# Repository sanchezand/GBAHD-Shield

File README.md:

# gbaHD Shield
This is a shield for the [gbaHD project](https://github.com/zwenergy/gbaHD).  

Has the following features.
- Connects via female headers to the Edge board (shield)
- Has a FFC 40, 32 and 34 pin connector for GBA LCD connector.
- Has a FFC 20 pin connector for controls with a wire up board.
- Has a ATMEGA328p for using a SNES Classic connector to control the GBA.
- **Both FFC cables need to be opposite side**

## Issues
- Havent had the chance to fully test the controller extension board, but the controller port on it works.
- Controller extension board needs to be made bigger and separate the button from the LED and the LED from the controller port.
- No case made for it yet
- GND pin on the breakout board needs to be moved (doesnt affect anything)
- Labels on breakout board need to be made bigger

## Contributing
If you wish to contribute, see something wrong or want to add a feature please make a pull request or leave an issue!

## BOM
|Reference	|Value								|
|---------	|--------							|
|C1, C2		|22pF									|
|C3			|100nF								|
|R1			|10K ohm									|
|R2			|120 ohm (or change for your LED)	|
|D1			|5mm LED or<br />TJ-L5FPTGCRMFCSFLC2R-A5	|
|U2			|ATMEGA328p-AU						|
|X1			|16MHz Crystal SMD-3225			|
|SW1			|XKB-TS-1185EC-C-D-B				|
|SW2			|XKB_XKB5858-Z-C					|
|J1			|JUSHUO_AFC01-S40FCC-00			|
|J2			|PinHeader 2x08 2.54mm			|
|J3, J9		|JUSHUO_AFC01-S20FCC-00			|
|J5			|JUSHUO_AFC07-S34FCC-00			|
|J7			|JUSHUO_AFC01-S32FCC-00			|
|J4			|PinHeader 2x10 2.54mm			|
|P1, P2		|Wii Expansion Port				|
|EXTRA 1		|PinHeader 1x08 2.54mm			|
|EXTRA 2		|PinHeader 1x06 2.54mm			|

## Programming the MCU
In order to program the MCU, you need an arduino to use as ISP.  
Use the following image to wire up an arduino to the board to program it.  
**I would also recomend not programming it while seated in the FPGA board.**
  
After wiring the board, follow this tutorial to flash the bootloader and the sketch to the board.  
[ICSP Tutorial](https://www.arduino.cc/en/pmwiki.php?n=Tutorial/ArduinoISP)  
  
The Arduino code requires the [NintendoExtensionCtrl](https://github.com/dmadison/NintendoExtensionCtrl) library.

## Version 1 vs Version 2
- __Removed SNES connector for an classic controller connector__
- Made the PCB bigger and uses lower pins to improve stability
- Added future proof pins to the edge board.
- Panelized the board to lower the amount of PCBs needed
- Added an "Expansion" board to relocate the controller port and add an LED and power switch (which needs to desolder old switch and be wired to the Spartan board)
- Made the breakout board bigger and added more extra pins.
- Changed FFC connectors (except 34 pin) to use a clamp down connector.

## Images

## LICENSE
This documentation describes Open Hardware and is licensed under the CERN OHL v. 1.2.
You may redistribute and modify this documentation under the terms of the CERN OHL v.1.2. (http://ohwr.org/cernohl). This documentation is distributed WITHOUT ANY EXPRESS OR IMPLIED WARRANTY, INCLUDING OF MERCHANTABILITY, SATISFACTORY QUALITY AND FITNESS FOR A PARTICULAR PURPOSE. Please see the CERN OHL v.1.2 for applicable conditions.

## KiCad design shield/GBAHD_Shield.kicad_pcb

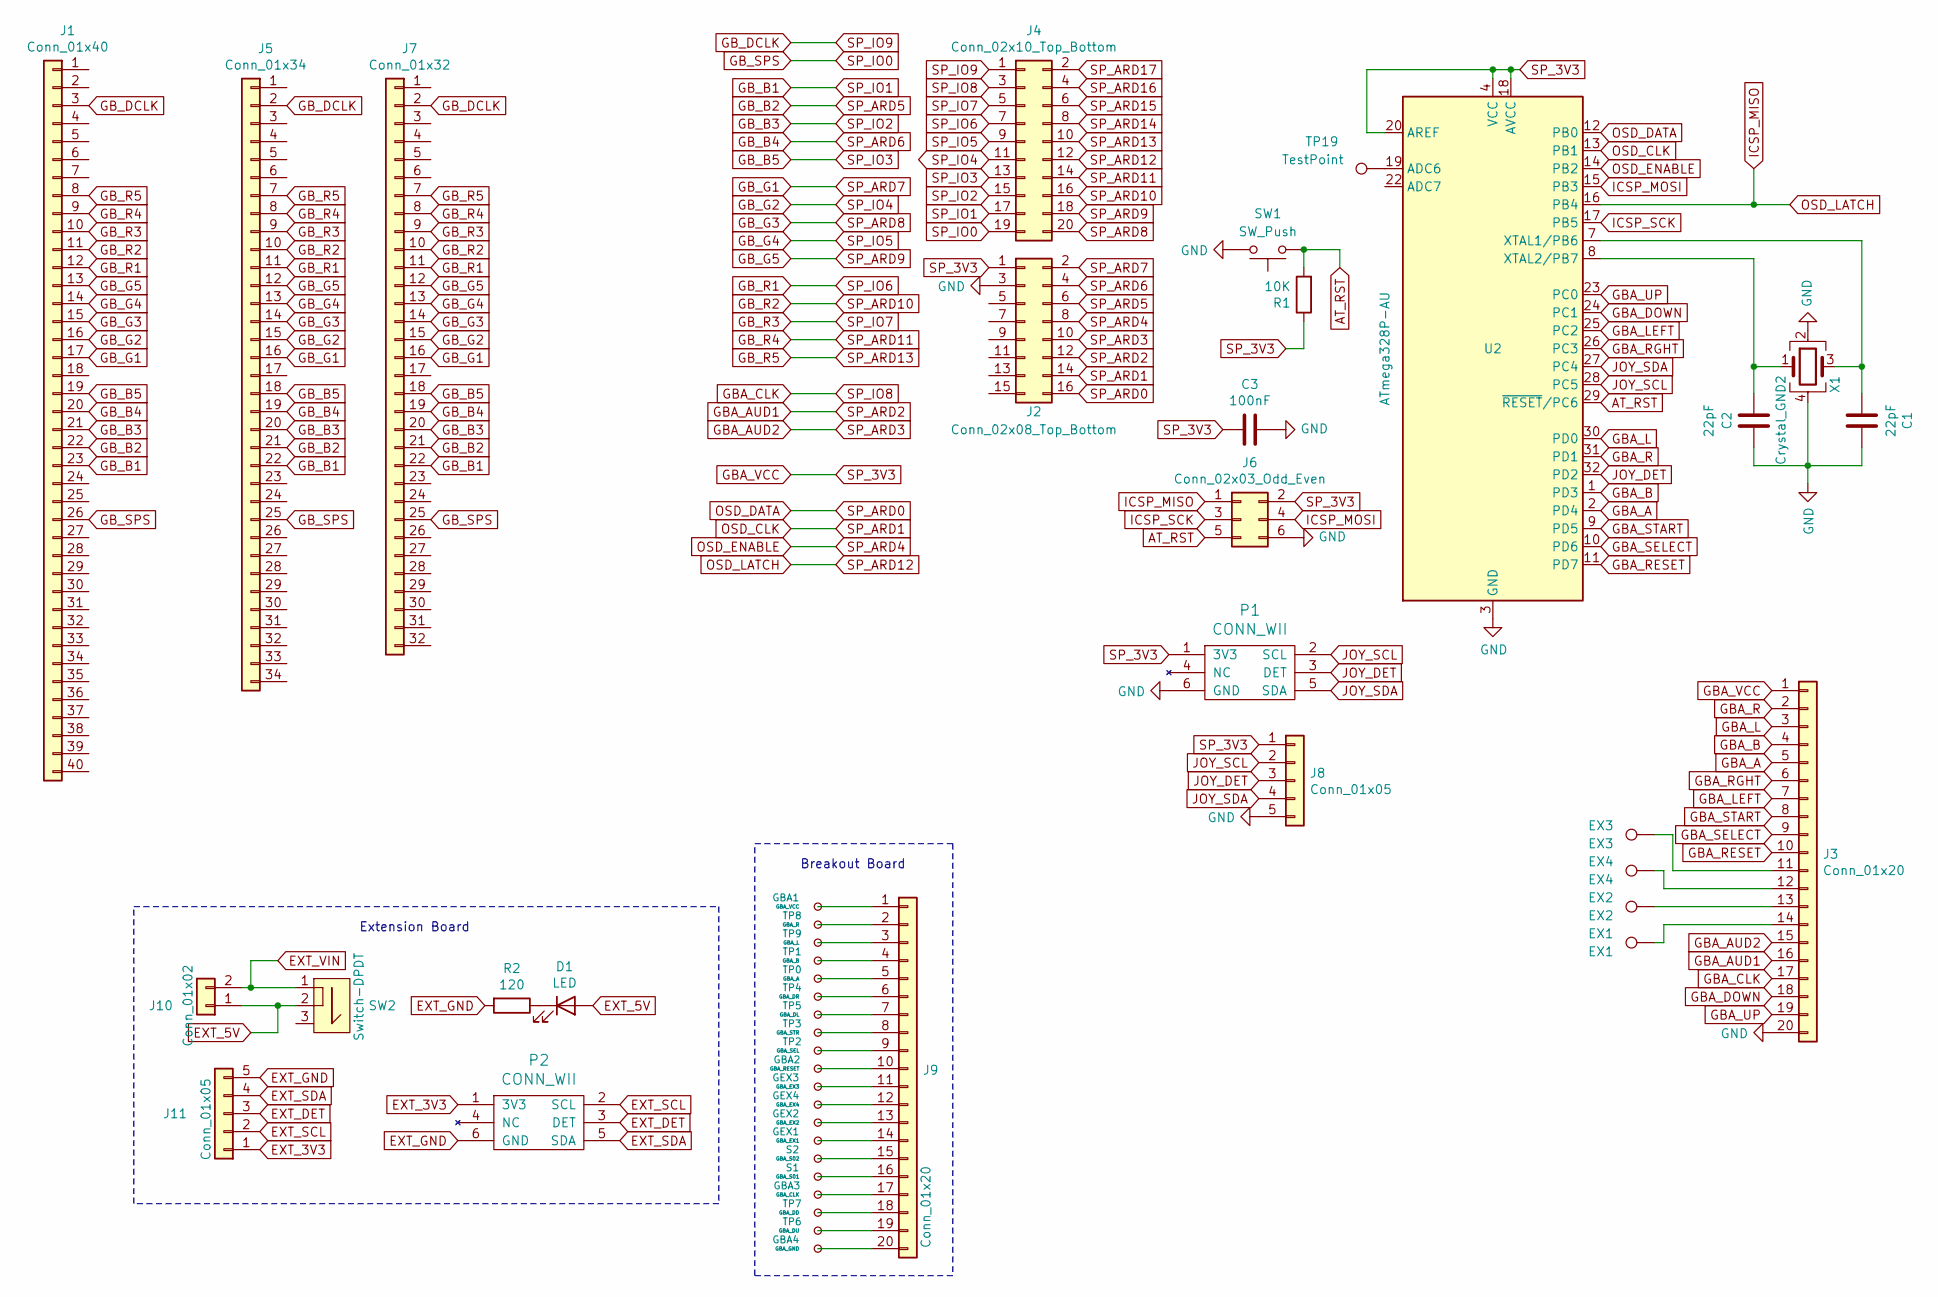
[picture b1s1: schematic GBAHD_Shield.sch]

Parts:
C1, C2: 22pF; C_0805_2012Metric_Pad1.18x1.45mm_HandSolder
C3: 100nF; C_0805_2012Metric_Pad1.18x1.45mm_HandSolder
D1: LED; LED_D5.0mm_FlatTop
EX1: EX1; SOLDER_PAD
EX2: EX2; SOLDER_PAD
EX3: EX3; SOLDER_PAD
EX4: EX4; SOLDER_PAD
GBA1: GBA_VCC; SOLDER_PAD
GBA2: GBA_RESET; SOLDER_PAD
GBA3: GBA_CLK; SOLDER_PAD
GBA4: GBA_GND; SOLDER_PAD
GEX1: GBA_EX1; SOLDER_PAD
GEX2: GBA_EX2; SOLDER_PAD
GEX3: GBA_EX3; SOLDER_PAD
GEX4: GBA_EX4; SOLDER_PAD
J1: Conn_01x40; JUSHUO_AFC01-S40FCC-00
J2: Conn_02x08_Top_Bottom; PinHeader_2x08_P2.54mm_Vertical
J3, J9: Conn_01x20; JUSHUO_AFC01-S20FCC-00
J4: Conn_02x10_Top_Bottom; PinHeader_2x10_P2.54mm_Vertical
J5: Conn_01x34; JUSHUO_AFC07-S34FCC-00
J6: Conn_02x03_Odd_Even; PinHeader_2x03_P2.54mm_Vertical
J7: Conn_01x32; JUSHUO_AFC01-S32FCC-00
J8, J11: Conn_01x05; PinHeader_1x05_P2.54mm_Horizontal
J10: Conn_01x02; PinHeader_1x02_P2.54mm_Horizontal
P1, P2: CONN_WII
R1: 10K; R_0805_2012Metric_Pad1.20x1.40mm_HandSolder
R2: 120; R_0805_2012Metric_Pad1.20x1.40mm_HandSolder
S1: GBA_S01; SOLDER_PAD
S2: GBA_S02; SOLDER_PAD
SW1: SW_Push; XKB-TS-1185EC-C-D-B
SW2: Switch-DPDT; XKB_XKB5858-Z-C
TP0: GBA_A; SOLDER_PAD
TP1: GBA_B; SOLDER_PAD
TP2: GBA_SEL; SOLDER_PAD
TP3: GBA_STR; SOLDER_PAD
TP4: GBA_DR; SOLDER_PAD
TP5: GBA_DL; SOLDER_PAD
TP6: GBA_DU; SOLDER_PAD
TP7: GBA_DD; SOLDER_PAD
TP8: GBA_R; SOLDER_PAD
TP9: GBA_L; SOLDER_PAD
TP19: TestPoint; SOLDER_PAD
U2: ATmega328P-AU; TQFP-32_7x7mm_P0.8mm
X1: Crystal_GND2; Crystal_SMD_3225-4Pin_3.2x2.5mm

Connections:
AT_RST: J6.5, R1.2, SW1.1, U2.29 (~RESET~/PC6)
EXT_3V3: J11.1, P2.1 (3V3)
EXT_5V: D1.2 (A), J10.1, SW2.2
EXT_DET: J11.3, P2.3 (DET)
EXT_GND: J11.5, P2.6 (GND), R2.2
EXT_SCL: J11.2, P2.2 (SCL)
EXT_SDA: J11.4, P2.5 (SDA)
EXT_VIN: J10.2, SW2.1
GBA_A: J3.5, U2.2 (PD4)
GBA_AUD1: J2.12, J3.16
GBA_AUD2: J2.10, J3.15
GBA_B: J3.4, U2.1 (PD3)
GBA_CLK: J3.17, J4.3
GBA_DOWN: J3.18, U2.24 (PC1)
GBA_L: J3.3, U2.30 (PD0)
GBA_LEFT: J3.7, U2.25 (PC2)
GBA_R: J3.2, U2.31 (PD1)
GBA_RESET: J3.10, U2.11 (PD7)
GBA_RGHT: J3.6, U2.26 (PC3)
GBA_SELECT: J3.9, U2.10 (PD6)
GBA_START: J3.8, U2.9 (PD5)
GBA_UP: J3.19, U2.23 (PC0)
GBA_VCC: C3.2, J2.1, J3.1, J6.2, J8.1, P1.1 (3V3), R1.1, U2.4 (VCC), U2.6 (VCC), U2.18 (AVCC), U2.20 (AREF)
GB_B1: J1.23, J4.17, J5.22, J7.22
GB_B2: J1.22, J2.6, J5.21, J7.21
GB_B3: J1.21, J4.15, J5.20, J7.20
GB_B4: J1.20, J2.4, J5.19, J7.19
GB_B5: J1.19, J4.13, J5.18, J7.18
GB_DCLK: J1.3, J4.1, J5.2, J7.2
GB_G1: J1.17, J2.2, J5.16, J7.16
GB_G2: J1.16, J4.11, J5.15, J7.15
GB_G3: J1.15, J4.20, J5.14, J7.14
GB_G4: J1.14, J4.9, J5.13, J7.13
GB_G5: J1.13, J4.18, J5.12, J7.12
GB_R1: J1.12, J4.7, J5.11, J7.11
GB_R2: J1.11, J4.16, J5.10, J7.10
GB_R3: J1.10, J4.5, J5.9, J7.9
GB_R4: J1.9, J4.14, J5.8, J7.8
GB_R5: J1.8, J4.10, J5.7, J7.7
GB_SPS: J1.26, J4.19, J5.25, J7.25
GND: C1.1, C2.1, C3.1, J2.3, J3.20, J6.6, J8.5, P1.6 (GND), SW1.2, U2.3 (GND), U2.5 (GND), U2.21 (GND), X1.2, X1.4
ICSP_MISO: J4.12, J6.1, U2.16 (PB4)
ICSP_MOSI: J6.4, U2.15 (PB3)
ICSP_SCK: J6.3, U2.17 (PB5)
JOY_DET: J8.3, P1.3 (DET), U2.32 (PD2)
JOY_SCL: J8.2, P1.2 (SCL), U2.28 (PC5)
JOY_SDA: J8.4, P1.5 (SDA), U2.27 (PC4)
unnamed: C1.2, U2.7 (XTAL1/PB6), X1.3
unnamed: C2.2, U2.8 (XTAL2/PB7), X1.1
unnamed: D1.1 (K), R2.1
unnamed: EX1.1, J3.14
unnamed: EX2.1, J3.13
unnamed: EX3.1, J3.11
unnamed: EX4.1, J3.12
unnamed: GBA1.1, J9.1
unnamed: GBA2.1, J9.10
unnamed: GBA3.1, J9.17
unnamed: GBA4.1, J9.20
unnamed: GEX1.1, J9.14
unnamed: GEX2.1, J9.13
unnamed: GEX3.1, J9.11
unnamed: GEX4.1, J9.12
unnamed: J9.2, TP8.1
unnamed: J9.3, TP9.1
unnamed: J9.4, TP1.1
unnamed: J9.5, TP0.1
unnamed: J9.6, TP4.1
unnamed: J9.7, TP5.1
unnamed: J9.8, TP3.1
unnamed: J9.9, TP2.1
unnamed: J9.15, S2.1
unnamed: J9.16, S1.1
unnamed: J9.18, TP7.1
unnamed: J9.19, TP6.1
unnamed: TP19.1, U2.19 (ADC6)
OSD_CLK: J2.14, U2.13 (PB1)
OSD_DATA: J2.16, U2.12 (PB0)
OSD_ENABLE: J2.8, U2.14 (PB2)
SP_ARD14: J4.8
SP_ARD15: J4.6
SP_ARD16: J4.4
SP_ARD17: J4.2

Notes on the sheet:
Breakout Board
Extension Board

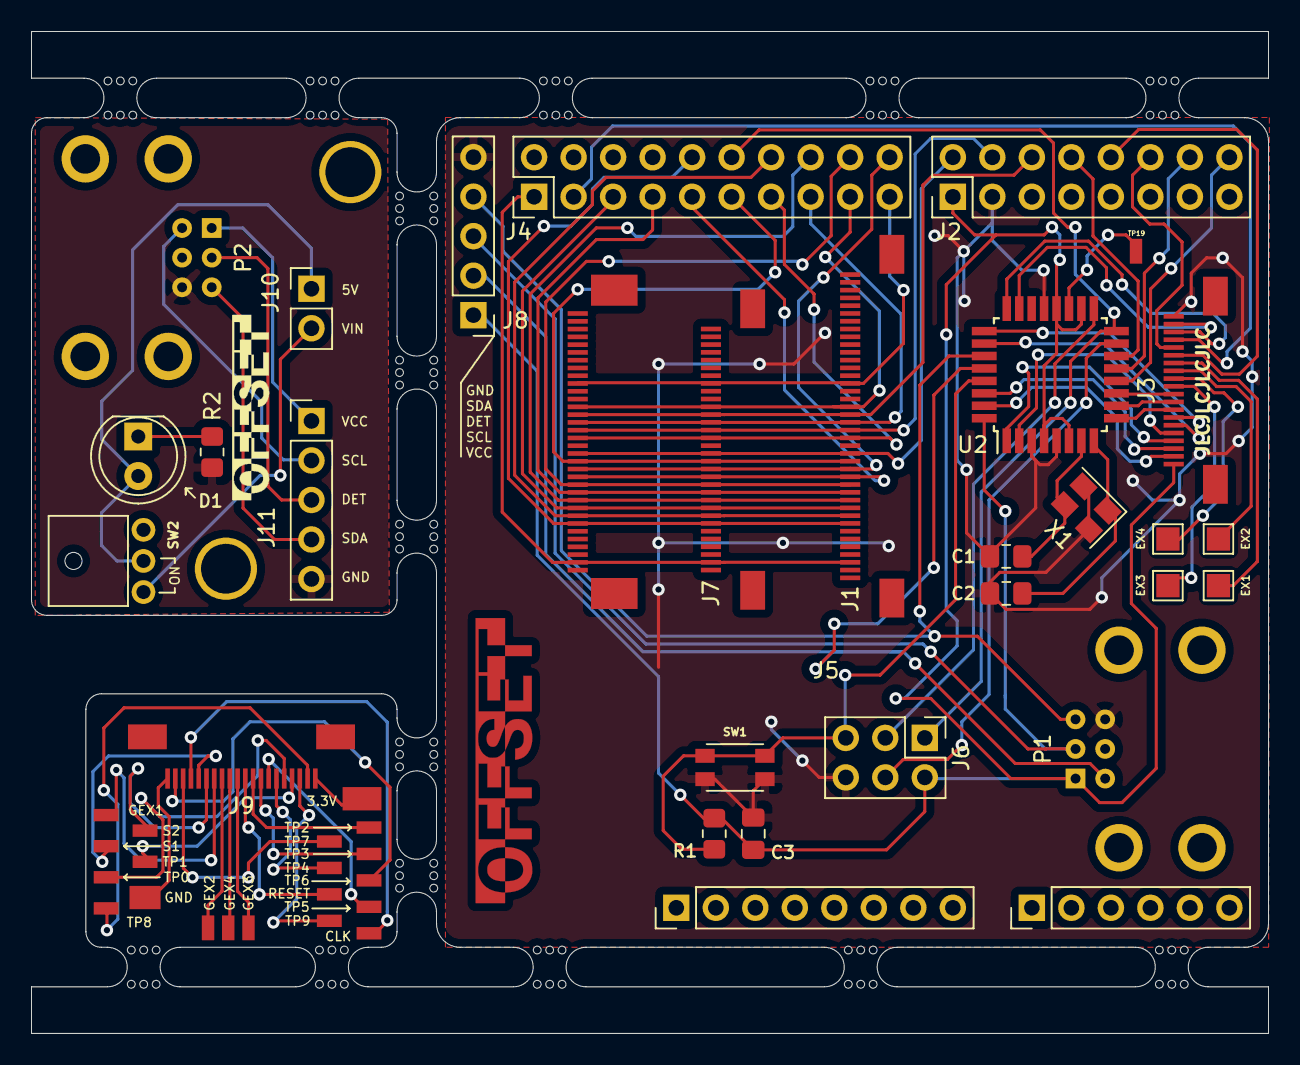
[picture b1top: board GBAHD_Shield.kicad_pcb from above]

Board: 2 copper layers, 79.5 x 64.4 mm, 67 parts (0 on the bottom side), 78 nets.

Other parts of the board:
EXP1: PinHeader_1x08_P2.54mm_Vertical
EXP2: PinHeader_1x06_P2.54mm_Vertical
HOLEM3, HOLEM3#2: VAL**; HOLE_M3
mousebite: VAL**; mouse-bite-2.54mm-slot
mousebite#2, mousebite#3, mousebite#4, mousebite#5, mousebite#6, mousebite#7, mousebite#8, mousebite#9, mousebite#10, mousebite#11, mousebite#12, mousebite#13, mousebite#14, mousebite#15: VAL**; mouse-bite-2.54mm-slot

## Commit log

2021-05-15 Version 2 initial commit.
    - Changed board layout
    - Changed breakout board pin order
    - Changed FFC connectors
    - Added connectors for 32 pin and 34 pin
    - Changed SNES connector to Classic connector.
2021-05-16 PCB changes and breakout board
    - Added breakout to main board as a breakaway board.
    - Added controller connector expansion for port relocation
    - Tidying routing and other minimal changes
2021-05-16 PCB design work
    - Added extension board (controller, LED and power switch)
    - Panelized board
2021-05-16 Removed old breakout PCB
2021-05-17 Added BOM, minor fixes
2021-05-17 Minor PCB changes
2021-05-25 Changed license to CERN OHL v1.2
2021-06-04 Updated v2 shield arduino sketch.
2021-06-04 Updated board files to include new trace.
2021-06-05 Changed OSD menu combination
2021-06-05 Fixed moved traces
